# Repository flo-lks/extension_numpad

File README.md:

# Extension Numpad
4x4 numpad to connect to your PC if you don't have one. The rotary encoder can be used to control the PC volume.
Future additions could include a way to switch between different keymaps to use it as a real macro pad.

[demo](https://youtu.be/KasFj6y4_b8)

## PCB
### Schematic

### PCB Layout

### PCB 3D Model

## Case
I use a sandwich-mount case design, which consists of a base and a top part. It is angled at 7 degrees for a more comfortable typing experience. The switches clip into the top plate, which is screwed to the base with the help of the heatset inserts.
Here are the OnShape Links to all parts: [Base](https://cad.onshape.com/documents/cdbf6aaf84bb518f5fc41afd/w/d72aa09dfed84ea584997cdd/e/9ded30b820c111a83a06e4c5?renderMode=0&uiState=69bbe44e727f4382826753fb), [Top](https://cad.onshape.com/documents/c205197f0eaaebc37cb0e7a9/w/398f6db9231d82ebe460adb4/e/7adaa80a929649ca5ef38242), [Rotarydial](https://cad.onshape.com/documents/0cc47eeeedf213fb4d3bd97f/w/859b01936aa7040036e683de/e/ecc9304a4732aee6efb41bf1), [Assembled](https://cad.onshape.com/documents/a27341ff84a250cd76250f05/w/721d63d8f915e883e9c7e543/e/c5b1b98a970bf75277e2f763)

## Firmware
This numpad uses the [QMK](https://qmk.fm/) firmware, with a basic numpad layout.

## BOM
| Qty | Part                                  |
|-----|---------------------------------------|
| 1   | 3D Printed Case (1x Base, 1x Top)     |
| 1   | EC11 (Switch) Rotary Encoder          |
| 1   | PCB                                   |
| 1   | Rotary Encoder Knob                   |
| 1   | Seeed Studio XIAO RP2040              |
| 2   | M3x16mm screws                        |
| 2   | M3x8mm screws                         |
| 4   | M3x5mx4mm heatset inserts             |
| 16  | Diodes (1N4148)                       |
| 16  | MX Keycaps                            |
| 16  | MX Style Switches                     |

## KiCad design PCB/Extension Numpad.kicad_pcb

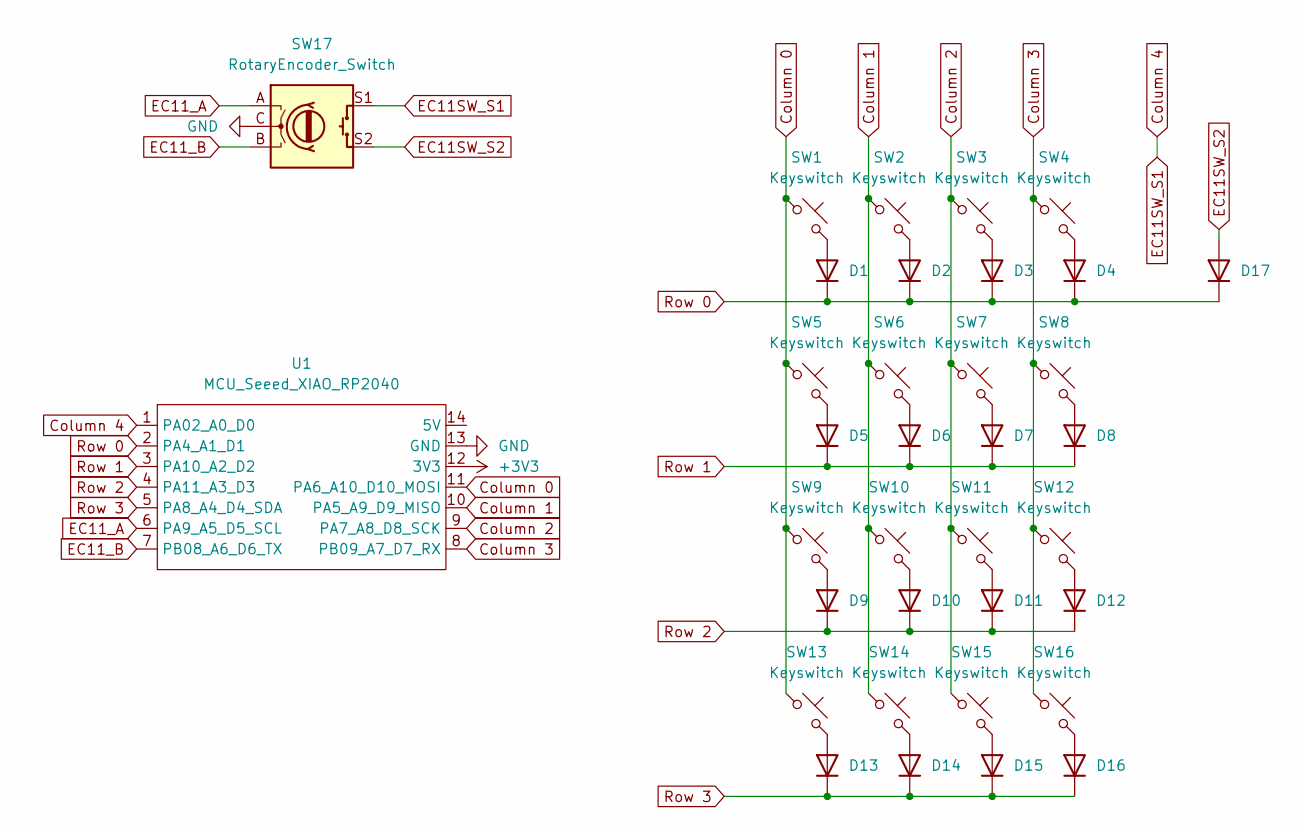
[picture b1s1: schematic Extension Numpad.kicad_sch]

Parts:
D1, D2, D3, D4, D5, D6, D7, D8, D9, D10, D11, D12, D13, D14, D15, D16, D17: 1N4148; Diode_DO-35
SW1, SW2, SW3, SW4, SW5, SW6, SW7, SW8, SW9, SW10, SW11, SW12, SW13, SW14, SW15, SW16: Keyswitch; MX_PCB_1.00u
SW17: RotaryEncoder_Switch; RotaryEncoder_Alps_EC11E-Switch_Vertical_H20mm
U1: MCU_Seeed_XIAO_RP2040; Seeed_XIAO_RP2040

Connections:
+3V3: U1.12 (3V3)
Column 0: SW1.1, SW5.1, SW9.1, SW13.1, U1.11 (PA6_A10_D10_MOSI)
Column 1: SW2.1, SW6.1, SW10.1, SW14.1, U1.10 (PA5_A9_D9_MISO)
Column 2: SW3.1, SW7.1, SW11.1, SW15.1, U1.9 (PA7_A8_D8_SCK)
Column 3: SW4.1, SW8.1, SW12.1, SW16.1, U1.8 (PB09_A7_D7_RX)
Column 4: SW17.S1, U1.1 (PA02_A0_D0)
EC11SW_S2: D17.2 (A), SW17.S2
EC11_A: SW17.A, U1.6 (PA9_A5_D5_SCL)
EC11_B: SW17.B, U1.7 (PB08_A6_D6_TX)
GND: SW17.C, U1.13 (GND)
unnamed: D1.2 (A), SW1.2
unnamed: D2.2 (A), SW2.2
unnamed: D3.2 (A), SW3.2
unnamed: D4.2 (A), SW4.2
unnamed: D5.2 (A), SW5.2
unnamed: D6.2 (A), SW6.2
unnamed: D7.2 (A), SW7.2
unnamed: D8.2 (A), SW8.2
unnamed: D9.2 (A), SW9.2
unnamed: D10.2 (A), SW10.2
unnamed: D11.2 (A), SW11.2
unnamed: D12.2 (A), SW12.2
unnamed: D13.2 (A), SW13.2
unnamed: D14.2 (A), SW14.2
unnamed: D15.2 (A), SW15.2
unnamed: D16.2 (A), SW16.2
Row 0: D1.1 (K), D2.1 (K), D3.1 (K), D4.1 (K), D17.1 (K), U1.2 (PA4_A1_D1)
Row 1: D5.1 (K), D6.1 (K), D7.1 (K), D8.1 (K), U1.3 (PA10_A2_D2)
Row 2: D9.1 (K), D10.1 (K), D11.1 (K), D12.1 (K), U1.4 (PA11_A3_D3)
Row 3: D13.1 (K), D14.1 (K), D15.1 (K), D16.1 (K), U1.5 (PA8_A4_D4_SDA)

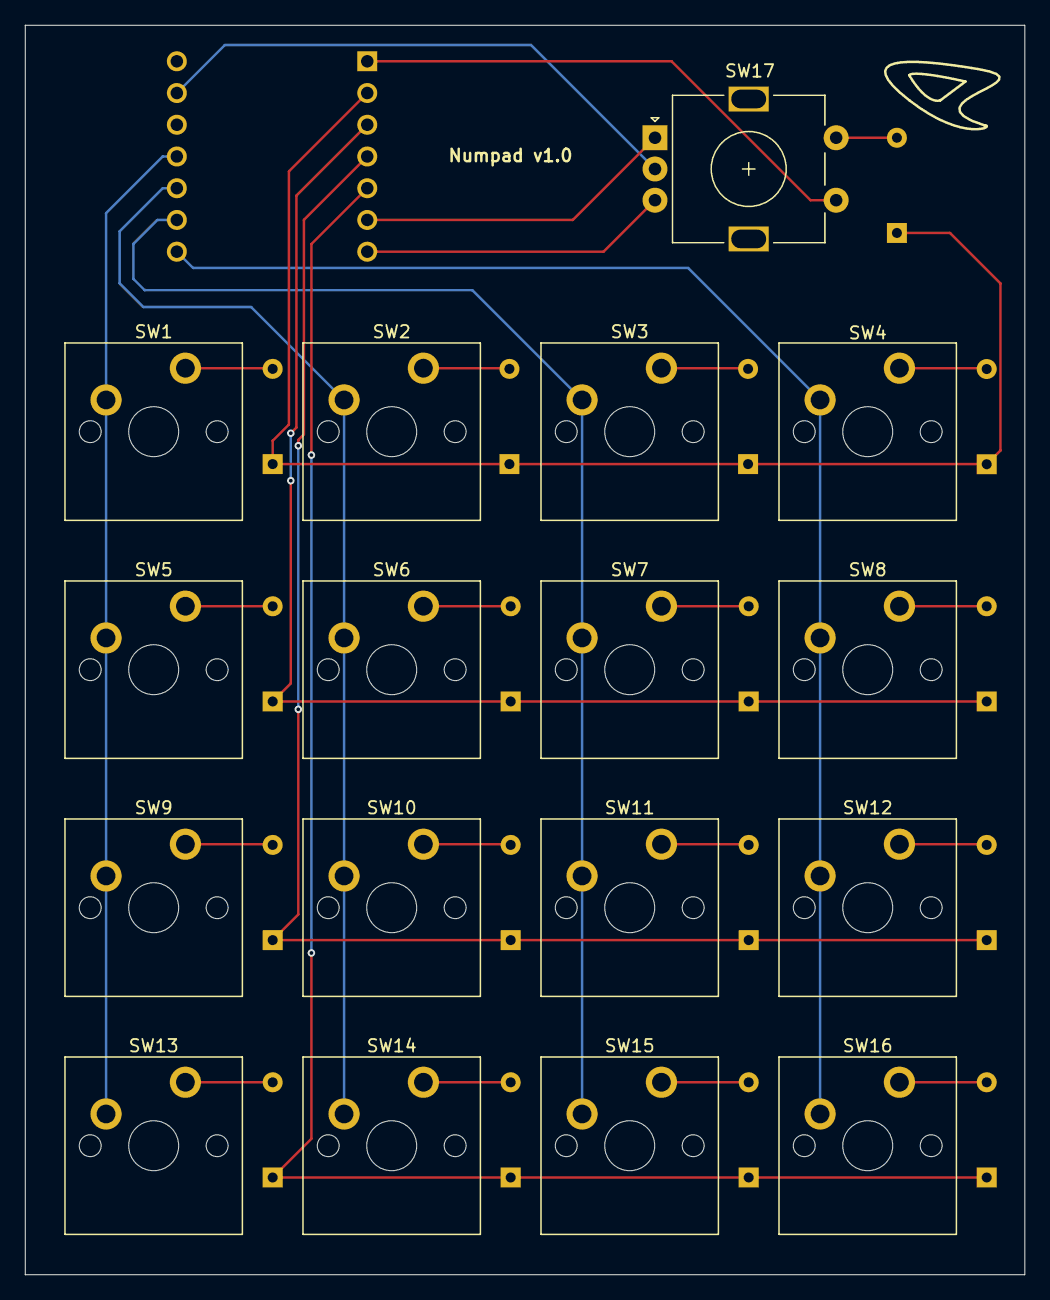
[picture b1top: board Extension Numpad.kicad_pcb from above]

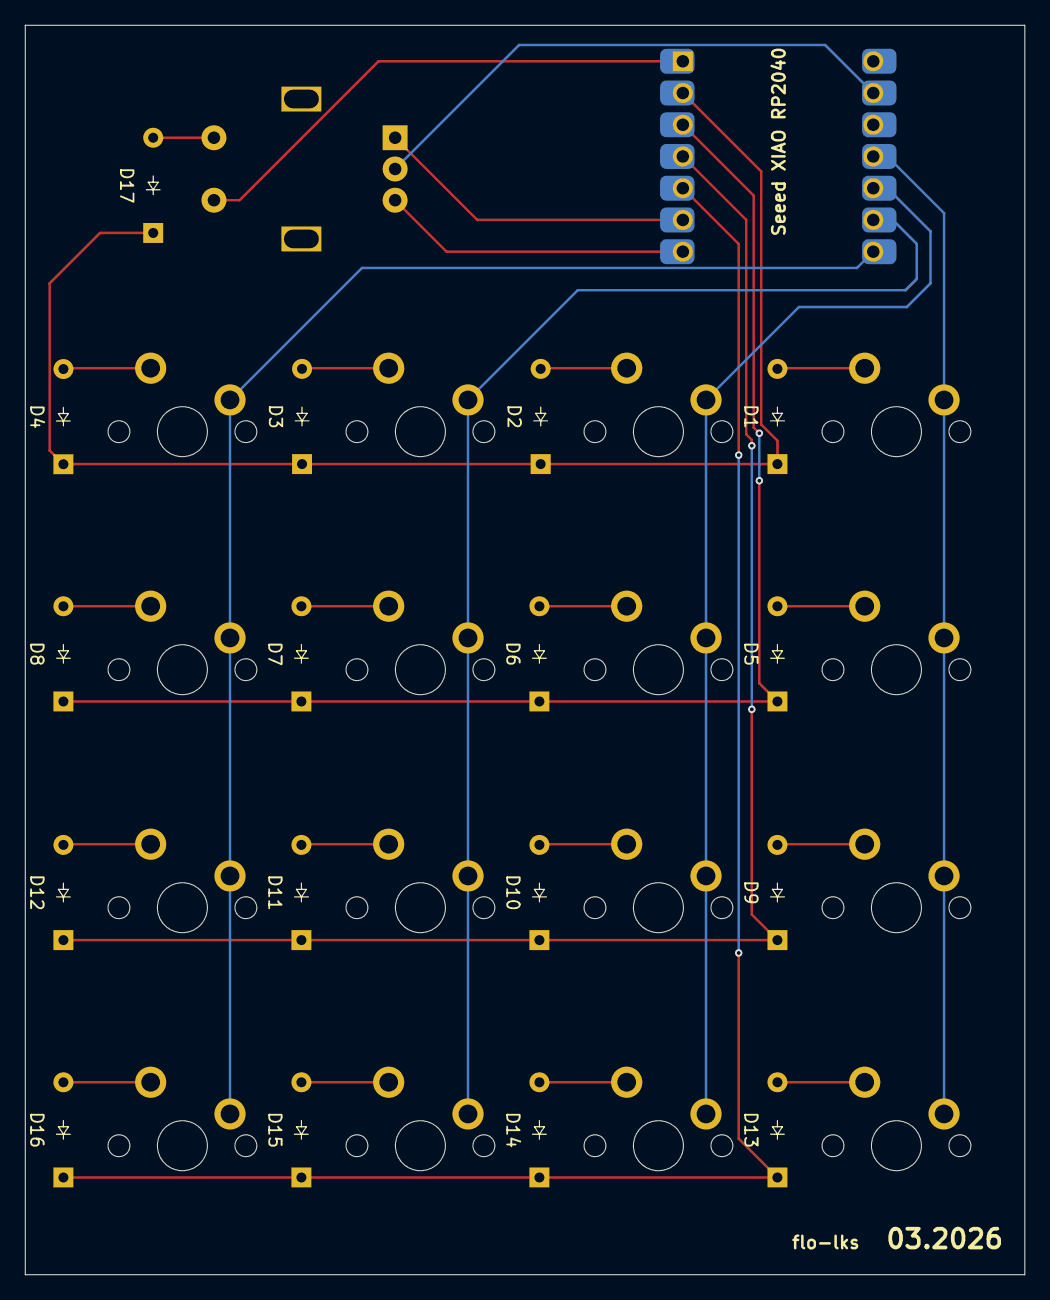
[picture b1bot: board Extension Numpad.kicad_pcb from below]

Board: 2 copper layers, 80.0 x 100.0 mm, 35 parts (18 on the bottom side), 29 nets.

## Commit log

2026-03-07 Add journal entry for extension numpad
2026-03-07 Update JOURNAL.md with project progress details
    Documented the initial setup and progress on the project.
2026-03-07 fix: images Header
2026-03-07 fix: image Header (now really)
2026-03-08 Designing the case in Fusion 360
2026-03-08 fix: resources link
2026-03-08 fix: resources link
    Corrected a broken link in the resources section of the journal entry.
2026-03-08 change picture
    Updated image link in JOURNAL.md and added a new image.
2026-03-11 Add entry for case design progress on 10.03.2026
2026-03-11 Add image
2026-03-11 Change date format in JOURNAL.md
    Updated the date format in the JOURNAL.md file.
2026-03-15 add files
2026-03-15 fix: render image file and keymap layout
2026-03-15 Fix image format and update firmware layout label
2026-03-15 add keymap image
2026-03-15 replace kaymap table with image
2026-03-15 Adjust keymap image size in README
2026-03-15 update format of BOM to table
2026-03-17 add: rotary encoder logic to firmware
2026-03-17 add: journal entry for 10.03.2026-17.03.2026
2026-03-19 add: PCB supports and f3d files
2026-03-19 add: OnShape links to README
2026-03-23 fix: hole dimensions and alignment
2026-03-23 fix: OnShape links for top and assembled
2026-03-31 Add: .stl files
2026-05-25 fix: keymap and encoder pin assignments
2026-05-25 add: journal entries and pictures to asstes
2026-05-26 add: final picture of numpad
2026-05-26 Add: MIT License
